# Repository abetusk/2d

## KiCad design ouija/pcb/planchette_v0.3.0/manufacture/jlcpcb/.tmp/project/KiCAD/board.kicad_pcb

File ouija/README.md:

Custom Ouija Board
===

An Ouija board that is completely in the public domain (CC0).

Artwork taken from [Legendes Bretonnes by Mourice de Becque](https://archive.org/details/legendesbret00becq/page/n38/mode/2up).

Font is [Rye](https://fonts.google.com/specimen/Rye#license).

---

| |
|---|
|  |

A simple design for an Ouija board.

Font is a slightly modified [Rye](https://fonts.google.com/specimen/Rye#license).

---

| |
|---|
|  |

A simple design for an Ouija board.

Font is a slightly modified [Rye](https://fonts.google.com/specimen/Rye#license).

Eye by Mike Rowe from the Noun Project [noun project](https://thenounproject.com/term/eye/19791/) (CC-BY).

Planchette outline taken from [phana007](https://www.thingiverse.com/thing:2732024) (CC-BY).

License
---

Unless explicitly indicated otherwise,
all files in this directory are licensed under a [CC0](https://creativecommons.org/share-your-work/public-domain/cc0/) license.

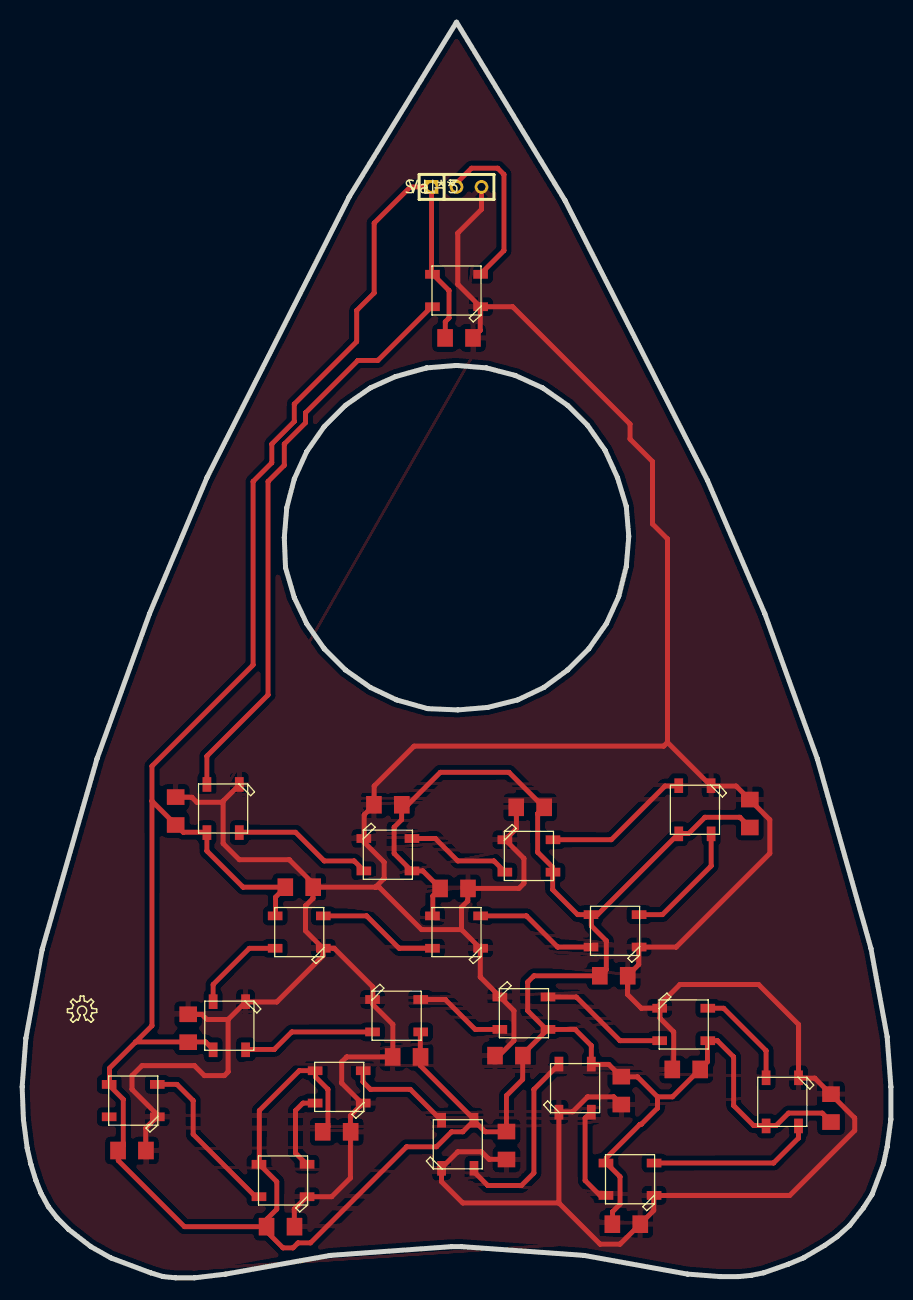
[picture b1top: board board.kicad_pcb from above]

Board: 5 copper layers, 88.4 x 127.8 mm, 40 parts (0 on the bottom side), 21 nets.

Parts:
SIL-3: Val**; SIL-3
c_ceye: C; C1206
c_cray: C; C1206
c_lbeye: C; C1206
c_lbray: C; C1206
c_llbray: C; C1206
c_lltray: C; C1206
c_lmeye: C; C1206
c_lstar: C; C1206
c_lteye: C; C1206
c_ltray: C; C1206
c_moon: C; C1206
c_rbeye: C; C1206
c_rbray: C; C1206
c_rmeye: C; C1206
c_rrbray: C; C1206
c_rrtray: C; C1206
c_rstar: C; C1206
c_rteye: C; C1206
c_rtray: C; C1206
d_ceye: val**; meowWS2812B
d_cray: val**; meowWS2812B
d_lbeye: val**; meowWS2812B
d_lbray: val**; meowWS2812B
d_llbray: val**; meowWS2812B
d_lltray: val**; meowWS2812B
d_lmeye: val**; meowWS2812B
d_lstar: val**; meowWS2812B
d_lteye: val**; meowWS2812B
d_ltray: val**; meowWS2812B
d_moon: val**; meowWS2812B
d_rbeye: val**; meowWS2812B
d_rbray: val**; meowWS2812B
d_rmeye: val**; meowWS2812B
d_rrbray: val**; meowWS2812B
d_rrtray: val**; meowWS2812B
d_rstar: val**; meowWS2812B
d_rteye: val**; meowWS2812B
d_rtray: val**; meowWS2812B
ref**: val**; OSHW-LOGO-S

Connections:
unnamed: SIL-3.1, c_ceye.1, c_cray.1, c_lbeye.1, c_lbray.1, c_llbray.1, c_lltray.1, c_lmeye.1, c_lstar.1, c_lteye.1, c_ltray.1, c_moon.1, c_rbeye.1, c_rbray.1, c_rmeye.1, c_rrbray.1, c_rrtray.1, c_rstar.1, c_rteye.1, c_rtray.1, d_ceye.1-VDD, d_cray.1-VDD, d_lbeye.1-VDD, d_lbray.1-VDD, d_llbray.1-VDD, d_lltray.1-VDD, d_lmeye.1-VDD, d_lstar.1-VDD, d_lteye.1-VDD, d_ltray.1-VDD, d_moon.1-VDD, d_rbeye.1-VDD, d_rbray.1-VDD, d_rmeye.1-VDD, d_rrbray.1-VDD, d_rrtray.1-VDD, d_rstar.1-VDD, d_rteye.1-VDD, d_rtray.1-VDD
unnamed: d_lstar.4-DIN, d_moon.2-DOUT
unnamed: SIL-3.2, d_moon.4-DIN
unnamed: SIL-3.3, c_ceye.2, c_cray.2, c_lbeye.2, c_lbray.2, c_llbray.2, c_lltray.2, c_lmeye.2, c_lstar.2, c_lteye.2, c_ltray.2, c_moon.2, c_rbeye.2, c_rbray.2, c_rmeye.2, c_rrbray.2, c_rrtray.2, c_rstar.2, c_rteye.2, c_rtray.2, d_ceye.3-GND, d_cray.3-GND, d_lbeye.3-GND, d_lbray.3-GND, d_llbray.3-GND, d_lltray.3-GND, d_lmeye.3-GND, d_lstar.3-GND, d_lteye.3-GND, d_ltray.3-GND, d_moon.3-GND, d_rbeye.3-GND, d_rbray.3-GND, d_rmeye.3-GND, d_rrbray.3-GND, d_rrtray.3-GND, d_rstar.3-GND, d_rteye.3-GND, d_rtray.3-GND
unnamed: d_rmeye.4-DIN, d_rstar.2-DOUT
unnamed: d_rstar.4-DIN, d_rteye.2-DOUT
unnamed: d_rrbray.4-DIN, d_rrtray.2-DOUT
unnamed: d_rbeye.2-DOUT, d_rrtray.4-DIN
unnamed: d_ceye.4-DIN, d_rmeye.2-DOUT
unnamed: d_ceye.2-DOUT, d_lmeye.4-DIN
unnamed: d_rbray.4-DIN, d_rrbray.2-DOUT
unnamed: d_lstar.2-DOUT, d_lteye.4-DIN
unnamed: d_lltray.4-DIN, d_lmeye.2-DOUT
unnamed: d_lbeye.4-DIN, d_lltray.2-DOUT
unnamed: d_lbray.4-DIN, d_ltray.2-DOUT
unnamed: d_cray.2-DOUT, d_ltray.4-DIN
unnamed: d_cray.4-DIN, d_rtray.2-DOUT
unnamed: d_rbray.2-DOUT, d_rtray.4-DIN
unnamed: d_lbeye.2-DOUT, d_rbeye.4-DIN
unnamed: d_lbray.2-DOUT, d_llbray.4-DIN
unnamed: d_lteye.2-DOUT, d_rteye.4-DIN

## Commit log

2018-12-04 link fix
2018-12-05 exporting gcode
2018-12-14 working on straing relief for panels..
2018-12-17 cc0 link
2018-12-20 license
2018-12-20 formatting and link to cc0
2018-12-20 fixing malformed sentence
2018-12-20 more specific (this directory)
2018-12-20 fixing spelling
2018-12-20 adding drafts
2018-12-20 adding some more steps, rename `notes.md` to `README.md` for ease of viewing
2018-12-20 laserweb4 link
2018-12-20 strain relief pics
2018-12-20 formatting pictures
2018-12-22 reenforcing paths to help make a better cut
2018-12-24 couture baisse
2018-12-26 final snake-pair pattern (and ngc)
2018-12-27 'production' version of anahart
2019-01-07 spelling
2019-01-15 adding links
2019-09-29 avacadolot
2019-09-29 just image
2019-09-29 license.
2019-10-02 hey, i like you
2021-04-26 adding parts (outline, innards)
